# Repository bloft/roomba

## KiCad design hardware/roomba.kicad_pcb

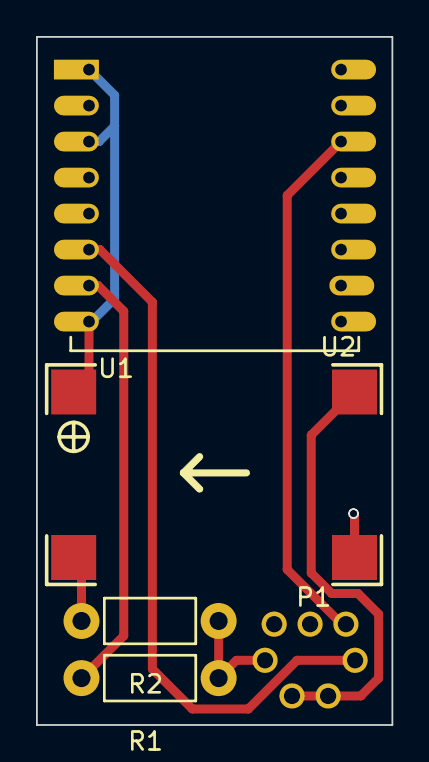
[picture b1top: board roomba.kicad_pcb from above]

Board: 2 copper layers, 19.7 x 38.2 mm, 5 parts (0 on the bottom side), 7 nets.

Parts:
P1: CONN_01X07; MiniDin-7
R1, R2: R; Resistor_Horizontal_RM7mm
U1: ESP-12
U2: 360_DC-DC; MINI-360

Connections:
+3V3: U1.1, U1.3, U1.8, U2.VOUT
/DD: P1.5, U1.14
/RX: P1.3, U1.6
/TX: P1.4, R1.1, R2.1
GND: P1.6, P1.7, R2.2, U1.9, U1.10, U2.GND
unnamed: R1.2, U1.7
VCC: P1.1, P1.2, U2.VIN
